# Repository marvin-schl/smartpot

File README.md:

# SmartPot

SmartPot ist ein RaspberryPi Projekt um einen smarten Blumentopf/Gewächshaus umzusetzen. Es werden alle für 
Pflanzen wichtigen Parameter (Temperatur, Luft-/Bodenfeuchtigkeit und Lichtstärke) gemessen und 
auf verschiedenen Wegen zur Verfügung stellt. Die Visualisierung der Daten kann über einen Webserver des 
Raspberry Pi´s aufgerufen und analysiert werden. Alternativ können die Sensorwerte auch per 
Telegram manuell erfragt werden. Außerdem können für alle Parameter kritische Schwellenwerte programmiert werden, bei deren 
Unter- bzw. Überschreiten eine Benachrichtigung über Telegram abgeschickt wird.
Im Folgenden wird die Umsetzung des Projektes detailliert dokumentiert, sodass mit Hilfe dieser 
Anleitung ein Nachbau des SmartPots möglich wird. Es werden alle Softwareeinrichtungsschritte von der Erstellung des Telegram Bots bis zur Node-RED Einrichtung erklärt. Außerdem werden Schaltpläne bereitgestellt welche auf die Softwareimplementationen angepasst sind. Zusätzlich zu den Schaltplänen wird ebenso ein Leiterplattenlayout, sowie alle benötigten Komponenten zum Bestücken der Leiterplatte mit einer Preisübersicht zur Verfügung gestellt.

Schaltungsseitig sind zur Zeit folgende Funktionalitäten implementiert:

- ein auf den RaspberryPi steckbares Shield mit integrierterm 12V/5V Linearregler zur Spannungsversorgung des Pi´s
- Anbindung eines Temperatur/Luftfeuchtigkeitssensors (DHT11/DHT22)
- Anbindung eines Bodenfeuchtigkeitssensors
- Anbindung eines Lichtsensors
- Drei schaltbare 12V/1,5A Leistungsausgänge mit PWM Unterstützung

Softwareseitig ist die aktuelle Version des SmartPots beinhaltet folgende Funktionen:

- _Temperatur_ messen, überwachen, auslesen und ausgeben
- _Luftfeuchtigkeit_ messen, überwachen,  auslesen und ausgeben
- _Bodenfeuchtigkeit_ messen, überwachen, auslesen und ausgeben
- _Lichtstärke_ messen, überwachen, auslesen und ausgeben
- Kommunikationsinterface über Telegram Web
- Node-RED Visualisierung der Sensorwerte (historisch/live)

Die Idee einen intelligenten Blumentopf zu entwickeln wurde durch zahlreiche Anleitungen aus dem
Web inspiriert (Bspw: [Automatisches Gewächshaus](https://tutorials-raspberrypi.de/automatisches-raspberry-pi-gewaechshaus-selber-bauen/)).

Der modulare Aufbau dieses Projektes eignet sich sehr gut für Gruppenarbeiten und kann dem
jeweiligen Wissensstand (Programmierung vom Raspberry Pi) durch Variation der
Funktionskomplexität angepasst werden.

In zukünftigen Versionen könnte unter einer optimierten Ausnutzung der verfügbaren Leistungsausgänge und Erweiterung von finanziellen Mitteln weitere Funktionen wie z.B. automatische Bewässerung, Lichtregelung sowie Belüftung realisiert werden, um so den Automatisierungsgrad weiter zu erhöhen.

## Gliederung

Diese Dokumentation glieder sich in folgende Schritte an denen unter Anderem die Inbetriebnahme des SmartPots erläutert wird:

1. Die Erstellung eines Telegram Bots 
2. Die Konfiguration des Telegram Bots für den SmartPot
3. Die Einrchtung von Node Red und der SmartPot Software selber 
    - 3.1 als manuelle Einichtung **oder**
    - 3.2  als automatische Einrchtung via docker und docker-compose
4. Die Bereitstellung der Schaltpläne und eines Leiterplattenlayout, zum Nachbau auf einem Bredboard oder zur Fertigung einer Leiterplatte, inklusive Stückliste aller benötigten Komponenten
5. Einer kurzen Übersicht der enthaltenen Klassen und Methoden 
6. Eine Übersicht, welche bekannten Schwachstellen und Verbesserungsideen für zukünftige Versionen des SmartPots existieren

## 1. Einrichtung des TelegramBots

Zunächst muss ein Chat mit dem Telegram-Bot „BotFather“ wie folgt erstellt werden:
Bei Telegram im Suchfeld „BotFather“ eingeben und unter Chats den BotFather auswählen.

Im Chat des BotFathers kann nun ein Chatbot erstellt werden:

1. /newbot eingeben
2. Botname vergeben
3. Username vergeben
4. Bot-Token kopieren
5. Link für Chatbot anklicken

Zum Abfragen neuer Nachrichten muss im Browser folgende Website aufgerufen werden:

https://api.telegram.org/botReplaceThisWithTheBotFatherToken/getUpdates

In Telegram Web dem erstellten Chatbot eine Nachricht senden. 

Nach Neuladen der Website kann nun aus der geschickten Nachricht die Chat-ID
ermittelt werden.

(Optional) Um den Chatbot einer Gruppe hinzufügen zu können, muss folgende Konfiguration im
BotFather vorgenommen werden:

1. /setprivacy eingeben
2. @Botname eingeben
3. Disable eingeben

***Achtung:** Wenn sich der Chatbot in einer Gruppe befindet, muss die Chat-ID der Gruppe verwendet werden!*

## 2. Konfiguration des SmartPots

Es wird davon ausgegangen, dass auf dem RaspberryPi ein neu installiertes RaspianOS basierend auf Debian Buster installiert, ein Zugang zum Internet, sowie ein ssh Zugang vorhanden ist. Zunächst muss dieses Repository auf dem RaspberryPi geclonet werden:

    git clone https://git.haw-hamburg.de/aco732/smartpot.git

Für die Konfiguration steht eine smartpot.ini Datei zur Verfügung. 

``` ini
#############################################
# Smart Pot Version 1 - Configuration File  #
#############################################

[Telegram]

#Sets the telepot API token
chattoken = <your-token>

#Sets the telepot Chat-ID
chatid = <your-chat-id>

[Logging]

# Sets the loglevel, when not specified DEBUG is taken
# Possible Values: INFO, WARN, ERROR, DEBUG
level = DEBUG

# If set to 1 the logs will be printed on sys.stdout
stdout = 1

# Sets the logfile
# Comment out to deactivate Logfile
file = smartpot.log

[Soil Moisture]
# This section calibrates the soil moisture sensor. Keep in mind that any calibration action will only effect the
# python software. Depending on the Calibration it is possible that the Node-RED settings have to updated manually

# Calibration of the soil moisture sensor connected to adc channel 1.
# The calibrated output value is calculated from the Output value out [V]  follows:
#     calibrated_out = scaling*(out - offset)
# Calibration procedure:
#    1.) Set both Values to zero.
#    2.) Connect the sensor and make sure it's 100% dry.
#    3.) Measure the voltage offset and adjust offset_calibration value to get an calibrated_out of 0.
#    4.) Pull the sensor onto a defined soil moisture level.
#    5.) Adjust scaling in such a way that calibratet_out matches the desired value.
# Default calibration is between 0 and 100% -> max Voltage 1.9V -> sclaing=100/1.9=52.6315
offset = 0.0
scaling = 52.6315

# Defines the level at which calibrated_out is going into saturation. Comment out
# to disable saturation.
saturation = 100

# Defines the unit of the measured and calibrated value. Percent Symbols have to be escaped with another percent symbol.
unit = "%%"

[Light]
# This section calibrates the light sensor. Keep in mind that any calibration action will only effect the
# python software. Depending on the Calibration it is possible that the Node-RED settings have to updated manually.

# Calibration of the light sensor connected to adc channel 2.
# The calibrated ouput value is calculated from the Output value out [V] as follows:
#     calibrated_out = scaling*(out - offset)
# Calibration procedure:
#    1.) Set both Values to zero.
#    2.) Connect the sensor and make sure it's completly dark.
#    3.) Measure the voltage offset and adjust offset_calibration value to get an calibrated_out of 0.
#    4.) Pull the sensor onto a defined brightness level.
#    5.) Adjust scaling in such a way that calibratet_out matches the desired value.
# Default calibration is between 0 and 100% -> max Voltage 1.8V -> sclaing=100/1.9=55.555
offset = 0.0
scaling = 55.555

# Defines the level at which calibrated_out is going into saturation. Comment out
# to disable saturation.
saturation = 100

# Defines the unit of the measured and calibrated value. Percent Symbols have to be escaped with another percent symbol.
unit = "%%"

```

In der Konfiguationsdatei müssen nun der zuvor ermittelte Telegram API-Token unter chattoken und die ermittelte Chat-ID unter chatid eingetragen werden. Außerdem können das Log-Level, das Ausgabeformat der Logs und die Kalibration der analogen Sensoren angepasst werden. 

Alternativ kann das setup.sh Skript ausgeführt werden, um die Telegram Konfiguration durchzuführen. Auf die abschließende Frage, ob der SmartPot via docker-compose gestartet werden soll, muss in diesem Fall mit "n" geantwortet werden:

    bash setup.sh

## 3.1 manuelle Einrichtung des RaspberryPi's

Zuerst müssen über Python Paketmanager pip folgende Pakete installiert werden.

    pip3 install RPi.GPIO Adafruit_DHT smbus2 telepot

Desweiteren wird eine [Library für den MCP3426](https://github.com/coburnw/MCP342x) für den MCP3426 verwendet. Diese ist bereits in den Source Files enthalten.

### Einrichten von Node-RED

Das Installation von Node-RED erfolgt durch folgende Shell-Eingabe:

    bash <(curl -sL https://raw.githubusercontent.com/node-red/linux-installers/master/deb/update-nodejs-and-nodered) --node16

Das Node-RED Dashboard zur Visualisierung der Sensorwerte wird mit folgender Eingabe installiert:

    npm i node-red-dashboard

Zusätzlich müssen in den Node-RED Einstellungen Parameter konfiguriert werden:

    cd ~/.node-red
    nano settings.js

@Line 253: „//“ entfernen

Um Node-RED bei Systemstart automatisch auszuführen wird folgender Befehl verwendet:

    sudo systemctl enable nodered.service

Der Node-RED Editor ist über die IP-Adresse des Pi´s aufzurufen. Die IP wird wie folgt angezeigt:

    hostname -l

Node-RED ist standardmäßig auf Port 1880 erreichbar. Mit dem im vorherigen Schritt ermittelten <hostname> kann die Node-RED Konfiguration unter folgender Adresse im Interetbrowser aufgerufen werden:
    
    http://<hostname>:1880

Die vorbereitete Node-RED Visualisierung kann nun wie folgt installiert werden:

1. Menü-Reiter auswählen
2. Palette verwalten klicken

3. „Dashboard“ in Suchfeld eingeben
4. Auf „Installieren“ klicken

Die zur Verfügung gestellte Visualisierung des Node-RED Dashboards muss nun wie folgt kopiert werden:

    cp /home/pi/smartpot/resources/flows.json /home/pi/.node-red/lib/flows

Abschließend wird die flow-Datei in Node-RED importiert:

1. Menü-Reiter auswählen
2. Import klicken

3. Lokal auswählen
4. „flows.json“ wählen

5. Auf „Import“ klicken
6. „Übernahme (deploy)“ klicken

Die Visualisierung kann nun unter 

    http://<hostname>:1880/ui

erreicht werden.

## 3.2 automatische Einrichtung des RaspberryPi's via Docker

Falls docker und docker-compose bereits installiert sein sollten kann der nächste Schritt übersprungen werden und direkt mit "Starten der Smartpot Umgebung" fortgefahren werden.

### Einrichtung von docker und docker-compose

Für die Einrichtung von docker und docker-compose müssen folgende Befehle ausgeführt werden.

    sudo apt-get update
    curl -sSL https://get.docker.com | sh
    sudo apt-get install docker-compose
    sudo usermod -aG docker pi

Nachdem der letzte Befehl ausfgeführt worden ist muss der Pi neugstartet werden.

   sudo reboot

### Starten der Smartpot Umgebung

Vor dem ersten Start muss die setup.sh ausgeführt werden. Diese stellt sicher, dass die ini, log und csv Dateien vorhanden sind und die Telegrameinstellungen getätigt worden sind. Außerdem stellt diese sicher, dass die Container mit ausreichenden Rechten gestartet werden:
    
    bash setup.sh
    
Der SmartPot kann gleich im Anschluss darauf us dem Skript heraus gestartet werden. **Sollte der Start nicht direkt aus der setup.sh erfolgen muss zuerst ein Neustart oder Neulogin durchgeführt werden!**
Aus dem SmartPot Verzeichnis kann nach Neustart/Neulogin in Zukunft der SmartPot wie folgt gestartet werden:

    docker-compose up
    
Um den SmartPot als Hintergrunddienst laufen und automatisch starten zu lassen, muss zusätzlich das Flag -d/--detached (losgelöst) verwendet werden:
    
    docker-compose up -d

## 4. elektronischer Aufbau

Schaltplan des RaspberryPi Shields:

Die Schaltung kann an einem handelsüblichen 12V Netzteil betrieben werden. Über einen 12V/5V Linearregler (uA78S05)
wird die Versorgnungsspannung für den RaspberryPi bereit gestellt. Auf dem Board ist eine dreipolige Buchsenleiste für einen DHT11 bzw DHT22 Sensor vorgesehen. Der Sensor kann einfach auf die Buchsenleiste gesteckt (Sensorseitig zur Platinenmitte zeigend) werden und per OneWire Protokoll ausgelesen werden. Für den analogen Lichtsensor und den analogen Bodenfeuchtigkeitssensors ist ein 2 Kanal Delta-Sigma AD-Wandler mit I2C Interface, der MCP3426, verbaut. Die drei Leistungsausgänge werden von drei P-Kanal Mosfets (AO3401A) geschaltet. Die Gate Signale werden durch einen Darlington-Array (ULN2003AD) getrieben, welches die Rohsignale des RaspberryPi verstärkt.
    
Für einen Betrieb des SmartPots über ein Bredboard muss in der aktuellen Version des SmartPots lediglich der DHT mit J1-12 und der MCP3426, zusätzlich zu seiner äußeren Beschaltung, mit den I2C-Pins J1-3 und J1-5 verbunden werden. Dann können die Sensoren analog zum o.g. Schaltplan ausgelesen werden. 
    
Die hier verwendeten analogen Sensoren geben Spannungen bis zu 4,2V  aus. Der MCP3426 kann an seinen differentiellen Eingängen jedoch nur Spannungen zwischen +-2,048V messen. Zur Reduktion der Eingangsspannung auf ein für den MCP3426 optimierten Spannungsniveau kann ein 1:1 Spannungsteiler (bswp: 10k-10k) verwendet werden. Dieser ist in den akuellen Schaltplänen und der Platine noch nicht vorgesehen. Aus diesem Grund wurde der Spannungsteiler in den beiden Sensorkabeln des Licht- und des Bodenfeuchtigkeitssensors verbaut.

Das dazugehörige Layout wurde wie folgt umgesetzt:

### Stückliste

Position    |Bezeichnung                        | Anzahl  |Stückpreis €| Positionspreis €
------------|-----------------------------------|-------- |------------|-----------------
1           | RaspberryPi 3B                    |1        |39,4        | 39,4
2           | RaspberryPi Staking Header        |1        |1,6         | 1,60
3           | ULN2003AD                         |1        |0,75        | 0,75
4           | 10k Kohleschichtwiderstand        |4        |0,1         | 0,4
5           | RPI LK Kabel 50                   |2        |2,75        | 5,50
6           | MCP3426                           |1        |3,10        | 3,10
7           | uA78S05                           |1        |0,45        | 0,45
8           | BD204                             |1        |0,41        | 0,41
9           | AO3401A                           |3        |0,25        | 0,75
10          | Widerstand 0805 1,0               |1        |0,03        | 0,03
11          | Widerstand 0805 2,0               |1        |0,02        | 0,02
12          | Widerstand 0805 51,0              |3        |0,02        | 0,06
13          | Widerstand 0805 5k                |2        |0,03        | 0,06
14          | Widerstand 0805 10k               |3        |0,03        | 0,09
15          | Keramikkondensator 0805 100nF     |1        |0,02        | 0,02
16          | Tantalkondensator 1210 10uF       |1        |0,32        | 0,32
17          | Elektrolytkondensator 2mm 1uF     |2        |0,02        | 0,04
18          | Elektrolytkondensator 5mm 1mF     |1        |0,29        | 0,29
19          | JST XH2P ST Buchse                |3        |0,20        | 0,60
20          | JST XH4P ST Buchse                |2        |0,25        | 0,50
21          | 3fach Buchsenleiste 2,54mm        |1        |0,14        | 0,14
22          | DC Buchse 2.1mm                   |1        |1,20        | 1,20
23          | DHT11                             |1        |4,50        | 4,50
24          | Joy-It Linker Kit Lichtsensor     |1        |1,01        | 1,01
25          | Joy-it sen-Moisture Sensorkit     |1        |4,99        | 4,99
26          | Leiterplatte                      |1        |2,00        | 2,00
27          | Gesamt                            |         |            | 68,23

(Reichelt Preise beispielhaft, Stand 06.01.22)

## 5. Software Implementation

Nachfolgend soll eine Klassenreferenz augestellt werden. Die einen Überblick über die implementierten Klassen und deren Methoden gib. Für eine genauere Beschreibung bitte die Methoden Kommentare beachten. Dort werden die einzelnen Argumente genauer beschrieben. 

**monitor.HysteresisMonitor**:
Diese Klasse implementiert die nicht blockierende Überwachung einer Ausgangsgröße. Es kann eine Funktion übergeben werden, welche den zu überwachenden Wert zurückgibt, ein oberer Grenzwert und ein unterer Grenzwert. Außerdem kann für das überschreiten des oberen und das unterschreiten des unteren Grenzwerts jeweils eine Callback Funktion übergeben werden. Diese Klasse erbt von threading.Thread. Eine Beispielhafte Verwendung dieser Klasse ist in example.py gegeben.

Öffentliche Methoden:
- start()
- stop()
- run()

**mointor.TimeBasedMonitor**:
Diese Klasse implementiert die nicht blockierende Überwachung einer Ausgangsgröße. Es kann eine Funktion übergeben werden, die die zu überwachende(n) Größe(n) zurückgibt. Diese Klasse erbt von threading.Thread. Eine Beispielhafte Verwendung dieser Klasse ist in example.py gegeben.

Öffentliche Methoden:
- start()
- stop()
- run()

**src.smartpot.SmartPot**:
Diese Klasse implementiert eine physikalische Repräsentation des SmartPots an sich und dient als Interface zum Backend. Es sind drei Konstanten vorhanden SmarPot.smarpot.SmartPot.X4, SmarPot.smarpot.SmartPot.X5 und SmarPot.smarpot.SmartPot.X6. Diese referenzieren die Leistungsausgänge auf dem SmartPot Raspberry Shield rev 1.1 und können den output_* Methoden als pin übergeben werden.
Öffentliche Methoden:
- output_on(pin)
- output_off(pin)
- output_pwm_on(pin, freq, dc)
- output_pwm_off(pin)
- output_pwm_change_freq(pin, freq)
- output_pwm_change_dc(pin, dc)
- read_temperature()
- read_humidity()
- read_light_intensity()
- read_soil_moisture()

**src.dht.DHT**:
Diese Klasse wrapped die Adafruit_DHT Library und stellt einen objektorientierten Zugriff zur Verfügung. Es kann bei der instanziierung festgelgt werden ob es sich um einen DHT11 oder DHT22 handelt.

Öffentliche Methoden:
- read_temperature()
- read_humidity()

**src.adc.MCP3426**:
Diese Klasse wrapped die verwendete [MCP342x](https://github.com/coburnw/MCP342x) Library für die hier benötigete Anwendung.

Öffentliche Methoden:
- read_ch1()
- read_ch2()

**src.output.PowerOutputPin**:
Diese Klasse verwendendet das RPi.GPIO Modul und implementiert die Funktionen der Leistungsausgänge. 

Öffentliche Methoden
- on()
- off()
- start_pwm(freq, dc)
- stop_pwm()
- change_freq(freq)
- change_dc(dc)

## 6. Ausblick

Hier werden bekannte Schwächen der aktuellen Version des SmartPots sowies des dazugehörige Shield aufgelistet, welche in folgenden Versionen überarbeitet werden sollten.

- Der Linearregler auf der pcb wird bei Betrieb mit einem 12V Netzteil und hohen Stromverbräuchen des Raspberrys sehr warm. Hier wäre eine Spannungswandlung über einen Schaltregler zu bevorzugen.

- Beim Ausschalten der Leistungsausgänge, also wenn das Gatesignal der Ausgangsmosfets (Q2, Q3, Q4) von 0V auf 12V gezogen wird. Findet die Entladung der Gatekapazität im unbelaseten Zustand über die Pullup Widerstände (R5, R6, R7) statt. Dies führt zumidest im unbelasteten Zustand zu sehr hohen Abfallszeit des Ausgangssignals. Ein Ansatz wäre kleinere Pullup Widerstände zu verwenden auf Kosten einer höheren Stromaufnahme bei eingeschaltetem Ausgang. Ein anderer Ansatz wäre die verwendung einer richtigen Mosfet Endstufe.

- In dem jetzigen Design wurden die positiven und negativen Ch2 Eingangspins des MCP3426 vertauscht. Die folgliche invertiert gemessene Spannung wurde Softwareseitig kompensiert.
    
- Die Ausgangssignale der analog Sensoren sind bis zu 4V hoch. Der MCP3426 kann jedoch nur +-2,048V messen. Eine Lösuing wäre ein auf der Leiterplatte befindlicher 1:1 Spannungsteiler, ein anderer AD-Wandler oder besser an den AD-Wandler angepasste Sensoren.

- Eine Verbesserung des Automatisierungsgrades durch die Nutzung der Hardwareseitig implementierten Schaltfunktionen

- Eine Erweiterung der Node-RED Oberflächen, sodass nicht nur ein passives Monitoring sondern auch eine aktive Kontrolle des SmartPots möglich ist

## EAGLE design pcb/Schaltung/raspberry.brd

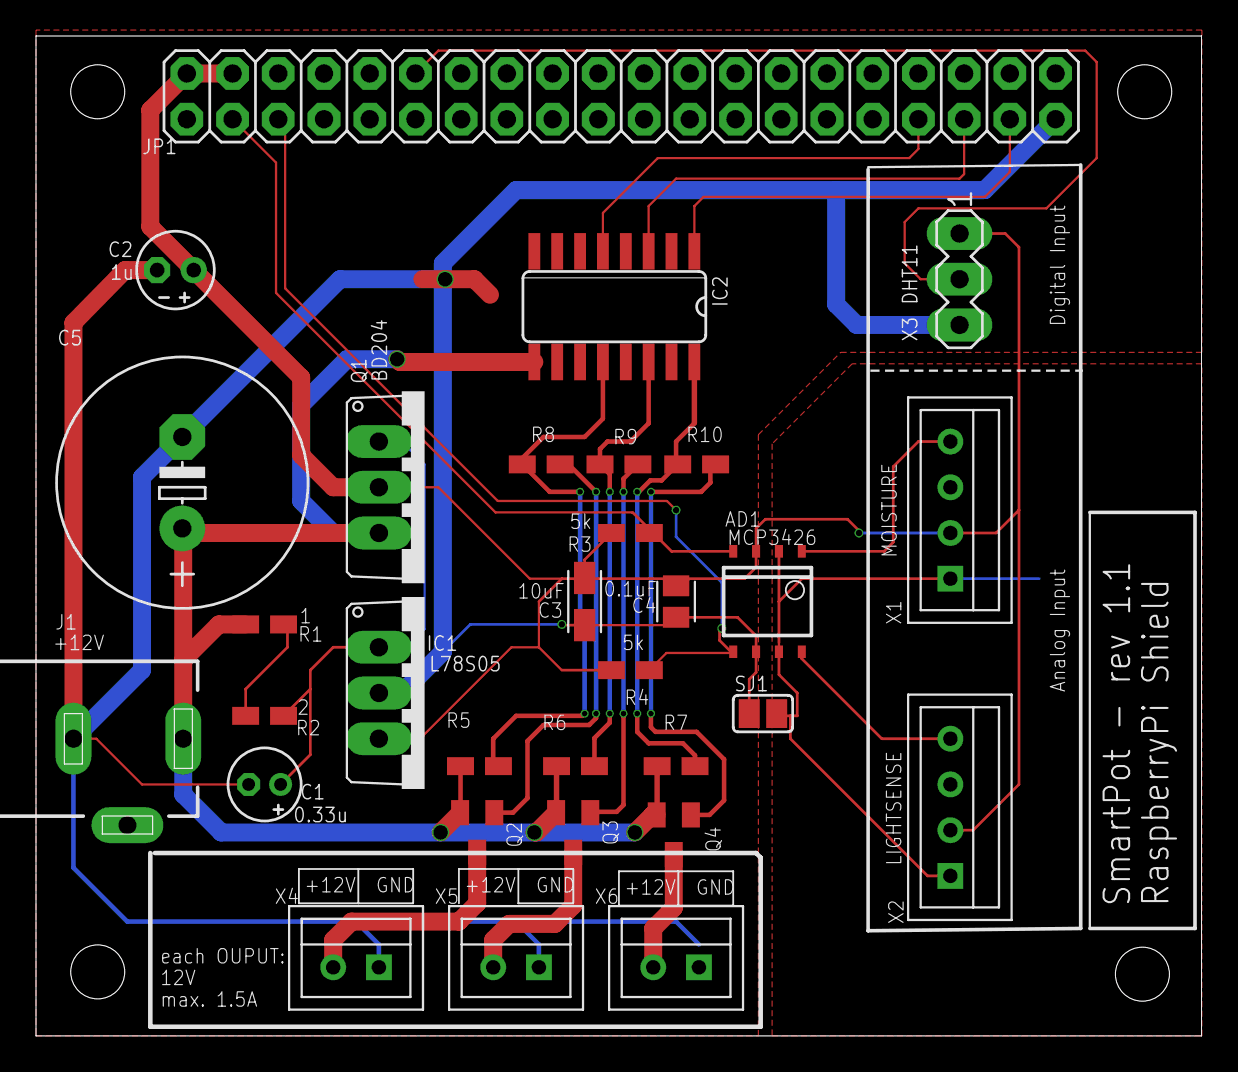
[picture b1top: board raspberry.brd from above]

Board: 2 copper layers, 64.8 x 55.5 mm, 31 parts (0 on the bottom side), 23 nets.

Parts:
AD1: MCP3426; SO-8
C1: 0.33u; E1,8-4
C2: 1u; E2-4
C3: 10uF; CAPM3216X180
C4: 0.1uF; CAPC2012X110
C5: 1000uF; E5-13
IC1: L78S05; TO220V
IC2: ULN2003AD; SO16
J1: DCJ0303
JP1: 2X20
Q1: BD204; TO220V
Q2, Q3, Q4: AO3401A; SOT23
R1: 1; R0805W
R2: 2; R0805W
R3, R4: 5k; R0805W
R5, R6, R7: 10k; R0805W
R8, R9, R10: 50; R0805W
SJ1: SJ
X1: MOISTURE; B4B-XH
X2: LIGHTSENSE; B4B-XH
X3: DHT11; MA03-1
X4, X5, X6: 02-JST; B2B-XH

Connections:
+5V: AD1.3, C2.+, C3.1, C4.1, IC1.3, JP1.2, JP1.4, Q1.2, R3.1, R4.1, X1.P$2, X2.P$2, X3.1
+12V: C5.+, IC2.9, J1.1, Q1.3, Q2.2, Q3.2, Q4.2, R1.2, R5.1, R6.1, R7.1
AGND: AD1.2, AD1.7, SJ1.2, X1.P$1, X2.P$1
GND: AD1.6, C1.-, C2.-, C3.2, C4.2, C5.-, IC1.2, IC2.8, J1.3, JP1.39, SJ1.1, X3.3, X4.P$1, X5.P$1, X6.P$1
GPIO18-DHT11-DATA: JP1.12, X3.2
unnamed: R1.1, R2.2
unnamed: AD1.4, JP1.3, R3.2
unnamed: C1.+, IC1.1, Q1.1, R2.1
unnamed: AD1.5, JP1.5, R4.2
unnamed: AD1.8, X2.P$4
unnamed: AD1.1, X1.P$4
unnamed: IC2.1, JP1.37
unnamed: Q3.3, X5.P$2
unnamed: Q4.3, X6.P$2
unnamed: IC2.3, JP1.35
unnamed: Q2.3, X4.P$2
unnamed: IC2.16, R7.2, R10.1
unnamed: Q2.1, R8.2
unnamed: IC2.5, JP1.33
unnamed: Q3.1, R9.2
unnamed: IC2.12, R5.2, R8.1
unnamed: IC2.14, R6.2, R9.1
unnamed: Q4.1, R10.2

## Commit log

2021-12-27 first smart pot version
2021-12-27 modified arguments of SmartPot constructor
2021-12-27 corrected names of output pins corresponding to naming on shield
2021-12-27 corrected dht pin from 21 to 18
2021-12-27 debugging adc channel2
2021-12-28 added mcp lib
2021-12-28 debugging adc
2021-12-28 added comments in SmartPot class
2021-12-28 added comments
2021-12-29 added threadsafe locks in classes where hardware access happens
2021-12-29 fixed some syntax errors
2022-01-06 logging message debug
2022-01-06 added some comments to HysterisMonitor class
2022-01-06 added some comments to TimeBasedMonitor class
2022-01-06 added schmeatics,gerber files and layout
2022-01-06 Telegram Kommunikation in Python Datei
2022-01-07 Telegram update
2022-01-07 adjusted unit of soil moisture and light sensor output
2022-01-07 NodeRed Flow Visualisierung
2022-01-07 Logging und TelegramBot Monitor Stops hinzugefügt
2022-01-08 adjusted max values of soil moisture and light sensor
2022-01-08 added config file
2022-01-08 Jason Node Red Datei Updated
2022-01-08 Node Red Flow änderung
2022-01-08 modified .gitignore
2022-01-08 added dockerfile
2022-01-08 Jason Datei Charts korregiert
2022-01-08 Upload New File
2022-01-08 Add new directory
2022-01-09 Kommentare in Telegramprogramm hinzugefügt
2022-01-09 dockerfile
2022-01-09 docker
2022-01-09 finished docker setup
2022-01-09 optimized docker setup
2022-01-09 modified docker configuration
2022-01-09 added logging option to std.out
2022-01-09 updated .gitignore
2022-01-09 final docker commit
2022-01-09 .gitignore test
2022-01-09 corrected logging
2022-01-09 merging
2022-01-10 final commit
2022-01-10 centralized logging setup
2022-01-10 stdout of smartpot container now outputs on docker-compose output
2022-01-10 reorganzied folders
2022-01-10 reafactored monitor.py
2022-01-10 added some configuration values
2022-01-10 extenden configuration capabilities
2022-01-10 reafactored logging
2022-01-10 debugging calibration
2022-01-10 changed Chart Reset Button to clear Logging.csv file and not to delete it
2022-01-11 updated gitignore
2022-01-11 added some comments in monitor class
2022-01-11 init commit
2022-01-11 resolved conflicts
2022-01-11 added startup script for docker-compose
2022-01-11 created setup.sh
2022-01-11 renamed start into setup
2022-01-11 modified setup.sh
2022-01-11 debugging dockerfile smartpot
2022-01-11 debugging dockerfile nodered
2022-01-11 updated smartpot.ini
2022-01-11 removed .idea
2022-01-11 reorganized folders
2022-01-14 Update dockerfile_smartpot
